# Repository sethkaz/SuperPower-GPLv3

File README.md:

# Super Power RPi Project

This repo was created to make a copy of the SuperPower-RPi project under the license GPLv3.

Please refer to the main Repo (https://github.com/SensorsIot/SuperPower) for the latest version.

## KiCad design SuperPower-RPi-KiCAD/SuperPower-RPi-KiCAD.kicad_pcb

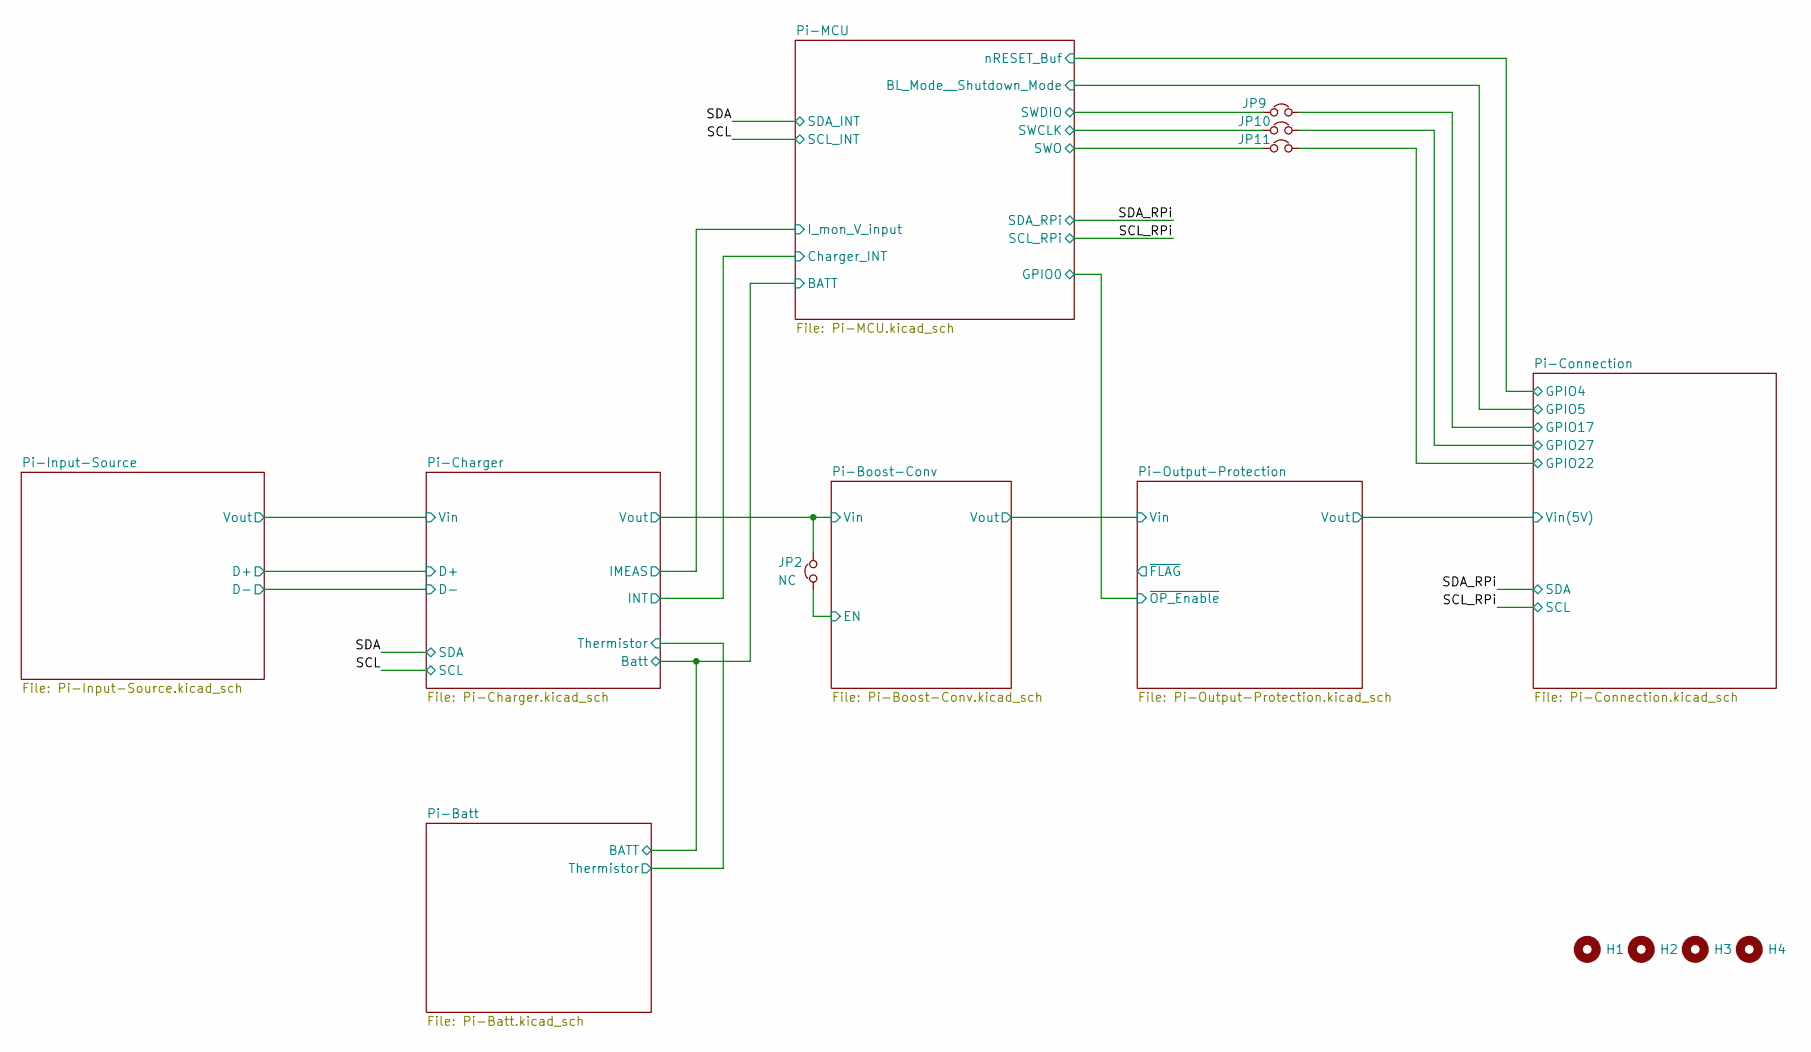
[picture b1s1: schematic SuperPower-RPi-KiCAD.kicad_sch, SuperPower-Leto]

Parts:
H1, H2, H3, H4: DNP; MountingHole_2.7mm_M2.5_ISO14580_Pad_TopBottom
JP2: NC; SolderJumper-2_P1.3mm_Bridged_Pad1.0x1.5mm
JP9, JP10, JP11: Jumper_NC_Small; SolderJumper-2_P1.3mm_Bridged_Pad1.0x1.5mm

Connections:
/Pi-Boost-Conv/EN: JP2.1; also elsewhere on the board
/Pi-Boost-Conv/Vin: JP2.2; also elsewhere on the board
/Pi-Connection/GPIO17: JP9.2; also elsewhere on the board
/Pi-Connection/GPIO22: JP11.2; also elsewhere on the board
/Pi-Connection/GPIO27: JP10.2; also elsewhere on the board
/Pi-MCU/SWCLK: JP10.1; also elsewhere on the board
/Pi-MCU/SWDIO: JP9.1; also elsewhere on the board
/Pi-MCU/SWO: JP11.1; also elsewhere on the board

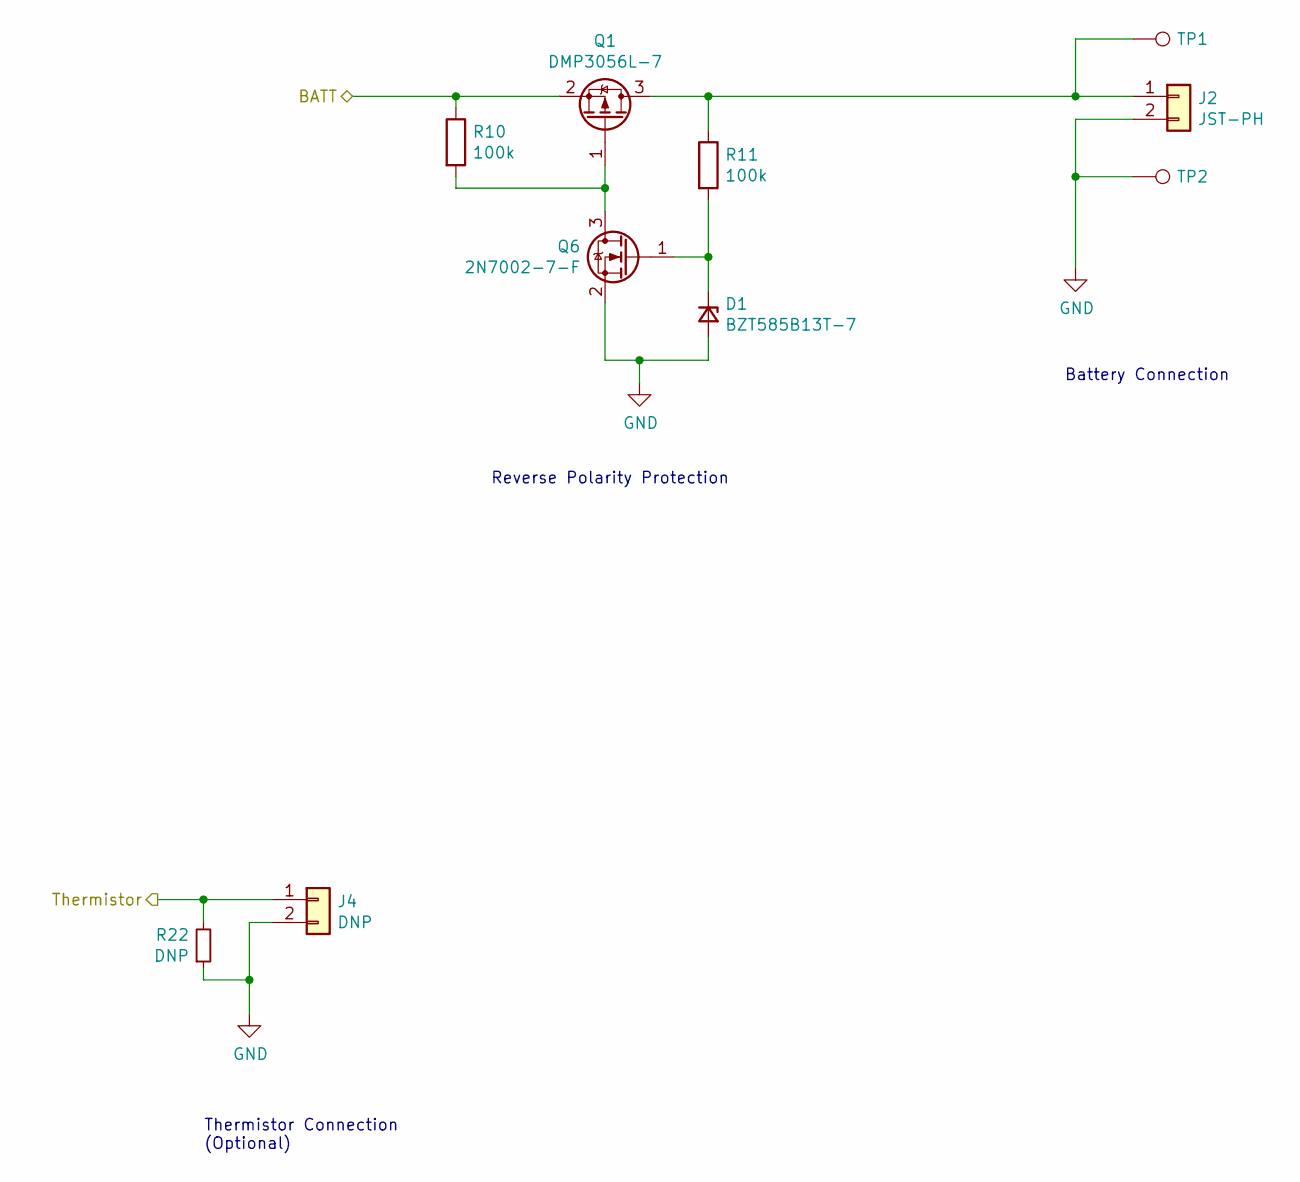
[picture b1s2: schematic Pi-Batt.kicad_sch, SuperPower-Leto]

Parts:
D1: BZT585B13T-7; D_SOD-523; Mfg PN BZT585B13T-7; Digi-Key PN BZT585B13T-7DICT-ND
J2: JST-PH; JST_PH_S2B-PH-K_1x02_P2.00mm_Horizontal; Mfg PN S2B-PH-K-S(LF)(SN)
J4: DNP; PinHeader_1x02_P2.00mm_Vertical; Mfg PN DNP
Q1: Q_PMOS_DMP3056L-7_SOT-23; SOT-23; Mfg PN DMP3056L-7; Digi-Key PN DMP3056L-7DICT-ND
Q6: 2N7002-7-F; SOT-23; Mfg PN 2N7002-7-F; Digi-Key PN 2N7002-FDICT-ND
R10, R11: 100k; R_0402_1005Metric; Mfg PN RC0402FR-07100KL; Digi-Key PN 311-100KLRCT-ND
R22: DNP; R_0603_1608Metric
TP1, TP2: DNP; SolderWire-1.5sqmm_1x01_D1.7mm_OD3.9mm

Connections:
/Pi-Batt/BATT: Q1.2 (S), R10.1; also elsewhere on the board
/Pi-Batt/Thermistor: J4.1, R22.2; also elsewhere on the board
GND: D1.2 (A), J2.2, J4.2, Q6.2 (S), R22.1, TP2.1; also elsewhere on the board
unnamed: D1.1 (K), Q6.1 (G), R11.2
unnamed: J2.1, Q1.3 (D), R11.1, TP1.1
unnamed: Q1.1 (G), Q6.3 (D), R10.2

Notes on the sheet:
Thermistor Connection (Optional)
Reverse Polarity Protection
Battery Connection

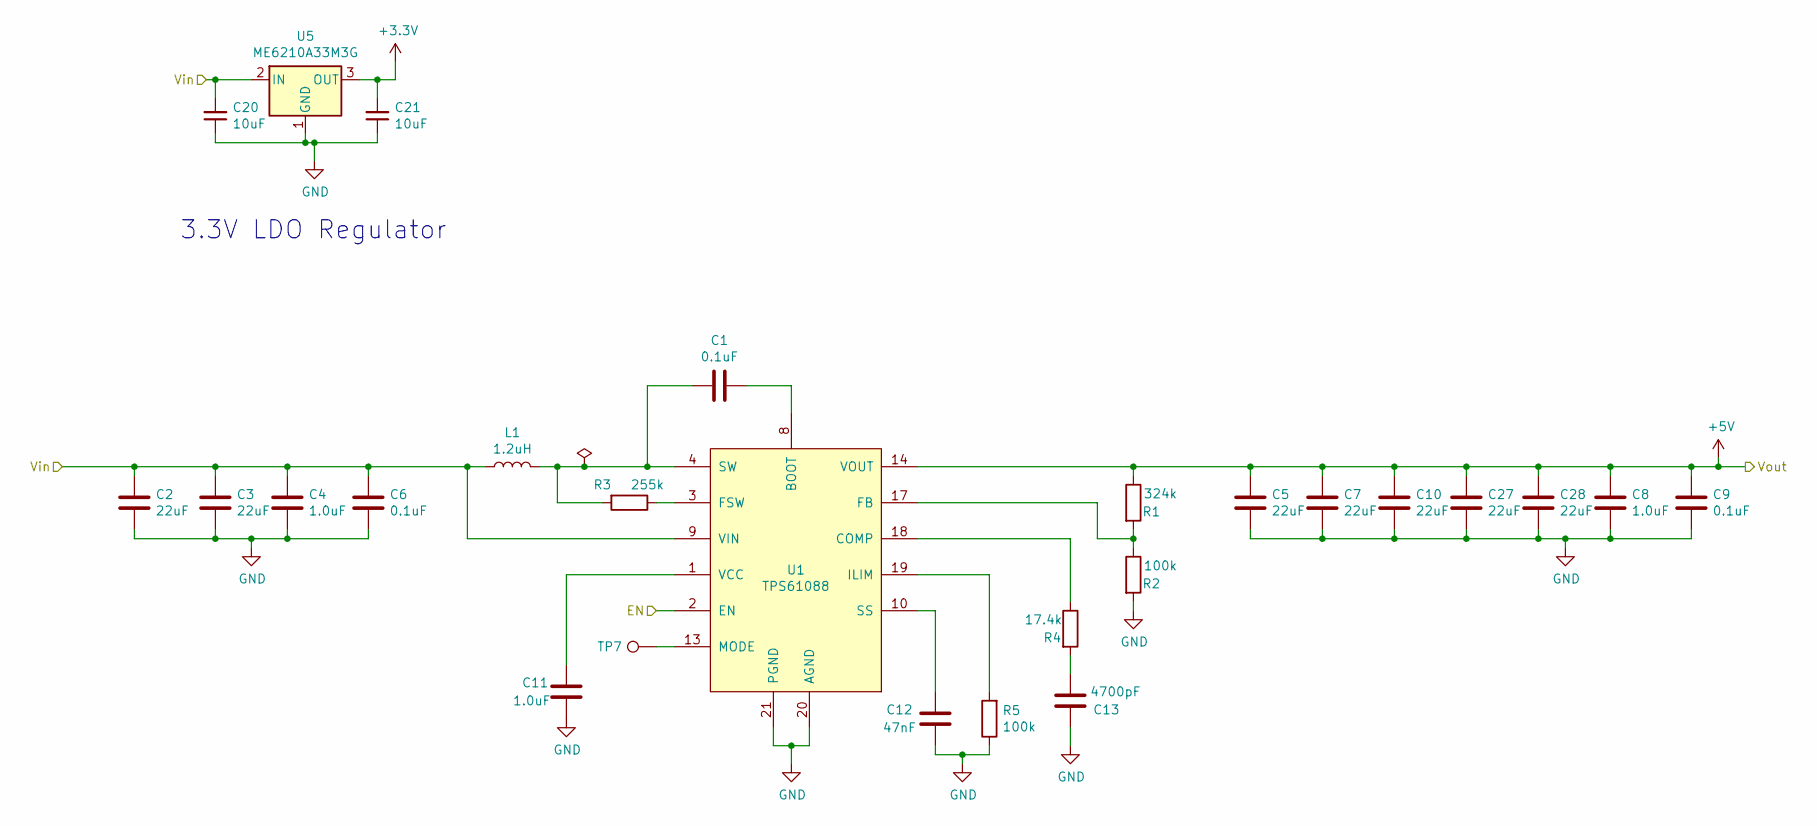
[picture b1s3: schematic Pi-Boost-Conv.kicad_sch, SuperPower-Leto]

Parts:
C1, C6, C9: 0.1uF; C_0402_1005Metric; Mfg PN TMK105BJ104KV-F; Digi-Key PN 587-1456-1-ND
C2, C3, C5, C7, C10, C27, C28: 22uF; C_1206_3216Metric; Mfg PN CL31A226KAHNNNE; Digi-Key PN 1276-3047-1-ND
C4, C8, C11: 1.0uF; C_0402_1005Metric; Mfg PN GRM155R61E105KA12D; Digi-Key PN 490-10017-1-ND
C12: 47nF; C_0402_1005Metric; Mfg PN GRM155R71E473KA88D; Digi-Key PN 490-3254-1-ND
C13: 4700pF; C_0402_1005Metric; Mfg PN CC0402KRX7R8BB472; Digi-Key PN 311-1039-1-ND
C20, C21: 10uF; C_0805_2012Metric; Mfg PN GRM21BR61E106KA73L; Digi-Key PN 490-5523-1-ND
L1: 1.2uH; L_Sumida_CDMC8D28_9.5x8.7mm; Mfg PN CDMC8D28NP-1R2MC; Digi-Key PN 308-1618-1-ND
R1: 324k; R_0402_1005Metric; Mfg PN ERJ-2RKF3243X; Digi-Key PN P324KLCT-ND
R2: 100k; R_0402_1005Metric; Mfg PN RC0402FR-07100KL; Digi-Key PN 311-100KLRCT-ND
R3: 255k; R_0603_1608Metric; Mfg PN RC0603FR-07255KL; Digi-Key PN 311-255KHRCT-ND
R4: 17.4k; R_0402_1005Metric; Mfg PN RC0402FR-0717K4L; Digi-Key PN 311-17.4KLRCT-ND
R5: 100k; R_0603_1608Metric; Mfg PN RC0603FR-07100KL; Digi-Key PN 311-100KHRCT-ND
TP7: DNP; TestPoint_Pad_1.0x1.0mm
U1: TPS61088; TI_VQFN_3.5x4.5mm; Mfg PN TPS61088RHLR; Digi-Key PN 296-43620-1-ND
U5: ME6210A33M3G; SOT-23; Mfg PN ME6210A33M3G

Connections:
+3V3: C21.2, U5.3 (OUT); also elsewhere on the board
+5V: C5.1, C7.1, C8.1, C9.1, C10.1, C27.1, C28.1, R1.1, U1.14 (VOUT), U1.15 (VOUT), U1.16 (VOUT); also elsewhere on the board
/Pi-Boost-Conv/EN: U1.2 (EN); also elsewhere on the board
/Pi-Boost-Conv/Vin: C2.1, C3.1, C4.1, C6.1, C20.2, L1.1, U1.9 (VIN), U5.2 (IN); also elsewhere on the board
GND: C2.2, C3.2, C4.2, C5.2, C6.2, C7.2, C8.2, C9.2, C10.2, C11.2, C12.1, C13.2, C20.1, C21.1, C27.2, C28.2, R2.2, R5.1, U1.11 (NC), U1.12 (NC), U1.20 (AGND), U1.21 (PGND), U5.1 (GND); also elsewhere on the board
unnamed: C1.1, U1.8 (BOOT)
unnamed: C1.2, L1.2, R3.2, U1.4 (SW), U1.5 (SW), U1.6 (SW), U1.7 (SW)
unnamed: C11.1, U1.1 (VCC)
unnamed: C12.2, U1.10 (SS)
unnamed: C13.1, R4.2
unnamed: R1.2, R2.1, U1.17 (FB)
unnamed: R3.1, U1.3 (FSW)
unnamed: R4.1, U1.18 (COMP)
unnamed: R5.2, U1.19 (ILIM)
unnamed: TP7.1, U1.13 (MODE)

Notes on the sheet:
3.3V LDO Regulator

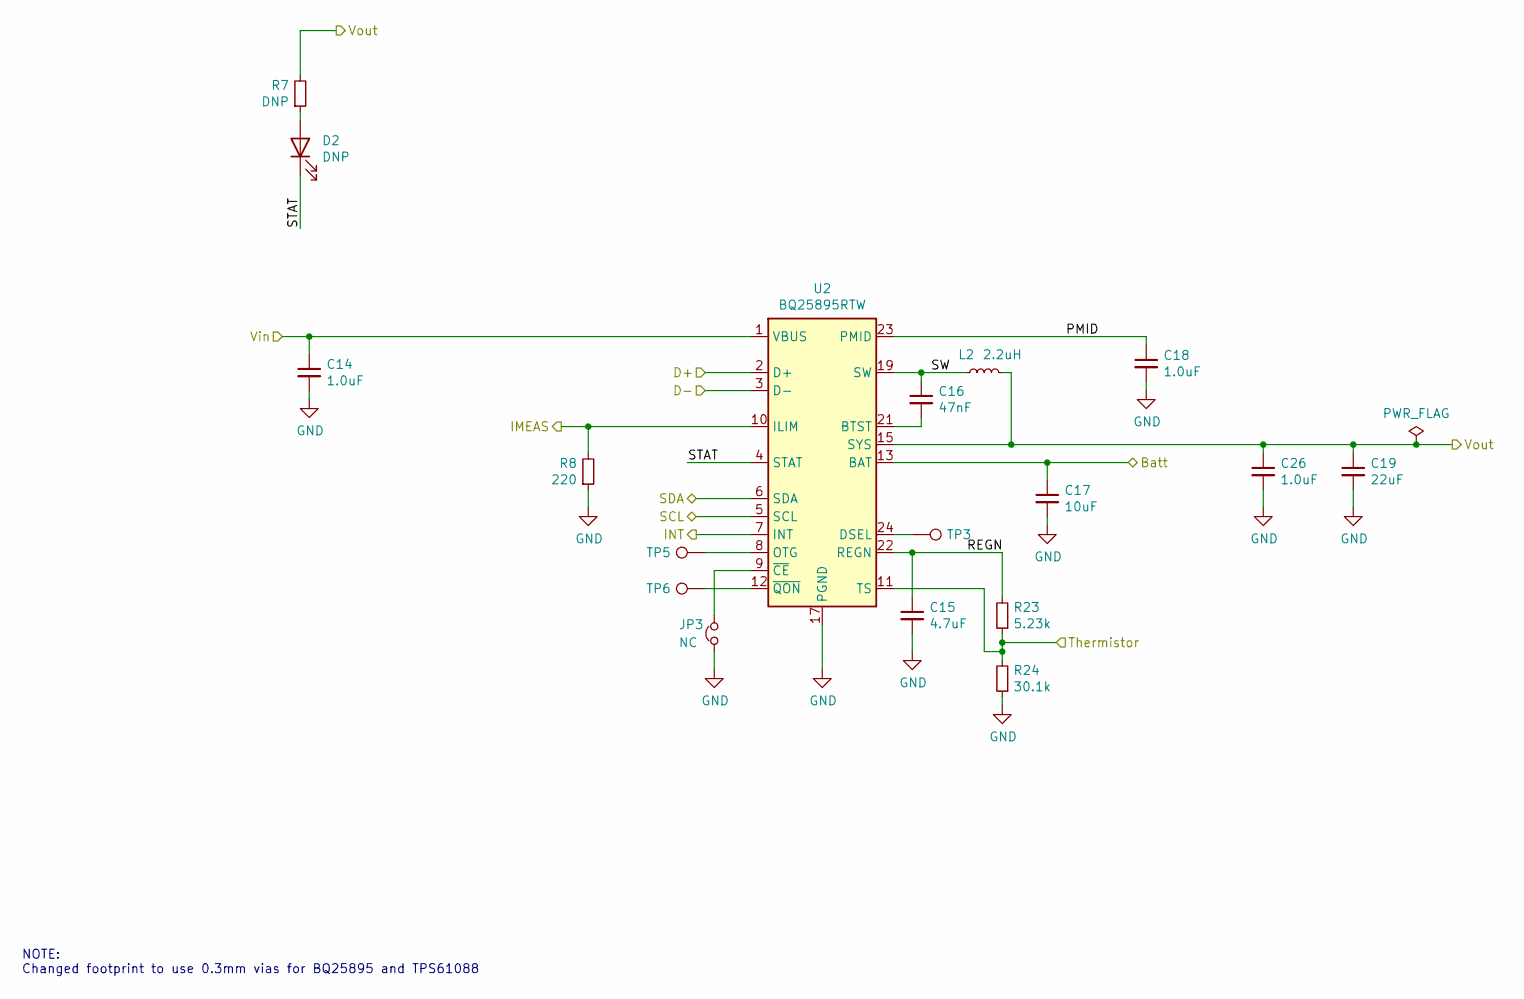
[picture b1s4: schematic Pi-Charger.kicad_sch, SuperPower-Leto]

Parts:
C14, C18, C26: 1.0uF; C_0402_1005Metric; Mfg PN GRM155R61E105KA12D; Digi-Key PN 490-10017-1-ND
C15: 4.7uF; C_0603_1608Metric; Mfg PN CL10A475KA8NQNC; Digi-Key PN 1276-1900-1-ND
C16: 47nF; C_0402_1005Metric; Mfg PN GRM155R71E473KA88D; Digi-Key PN 490-3254-1-ND
C17: 10uF; C_0805_2012Metric; Mfg PN GRM21BR61E106KA73L; Digi-Key PN 490-5523-1-ND
C19: 22uF; C_1206_3216Metric; Mfg PN CL31A226KAHNNNE; Digi-Key PN 1276-3047-1-ND
D2: DNP; LED_0603_1608Metric
JP3: NC; SolderJumper-2_P1.3mm_Bridged_Pad1.0x1.5mm
L2: 2.2uH; L_Vishay_IHLP-2525; Mfg PN IHLP2525CZER2R2M01; Digi-Key PN 541-1008-1-ND
R7: DNP; R_0603_1608Metric
R8: 220; R_0603_1608Metric; Mfg PN RC0603FR-07220RL; Digi-Key PN 311-220HRCT-ND
R23: 5.23k; R_0603_1608Metric; Mfg PN RC0603FR-075K23L; Digi-Key PN 311-5.23KHRCT-ND
R24: 30.1k; R_0603_1608Metric; Mfg PN RC0603FR-0730K1L; Digi-Key PN 311-30.1KHRCT-ND
TP3, TP5, TP6: DNP; TestPoint_Pad_1.0x1.0mm
U2: BQ25895RTW; Texas_S-PWQFN-N24_EP2.7x2.7mm_ThermalVias; Mfg PN BQ25895RTWR; Digi-Key PN 296-44345-1-ND

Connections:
/Pi-Batt/BATT: C17.1, U2.13 (BAT), U2.14 (BAT); also elsewhere on the board
/Pi-Batt/Thermistor: R23.1, R24.2, U2.11 (TS); also elsewhere on the board
/Pi-Boost-Conv/Vin: C19.1, C26.1, L2.2, R7.2, U2.15 (SYS), U2.16 (SYS); also elsewhere on the board
/Pi-Charger/D+: U2.2 (D+); also elsewhere on the board
/Pi-Charger/D-: U2.3 (D-); also elsewhere on the board
/Pi-Charger/IMEAS: R8.2, U2.10 (ILIM); also elsewhere on the board
/Pi-Charger/PMID: C18.1, U2.23 (PMID)
/Pi-Charger/REGN: C15.1, R23.2, U2.22 (REGN)
/Pi-Charger/STAT: D2.1 (K), U2.4 (STAT)
/Pi-Charger/SW: C16.1, L2.1, U2.19 (SW), U2.20 (SW)
/Pi-Charger/Vin: C14.1, U2.1 (VBUS); also elsewhere on the board
/Pi-MCU/Charger_INT: U2.7 (INT); also elsewhere on the board
/SCL: U2.5 (SCL); also elsewhere on the board
/SDA: U2.6 (SDA); also elsewhere on the board
GND: C14.2, C15.2, C17.2, C18.2, C19.2, C26.2, JP3.1, R8.1, R24.1, U2.17 (PGND), U2.18 (PGND), U2.25 (PGND); also elsewhere on the board
unnamed: C16.2, U2.21 (BTST)
unnamed: D2.2 (A), R7.1
unnamed: JP3.2, U2.9 (~CE)
unnamed: TP3.1, U2.24 (DSEL)
unnamed: TP5.1, U2.8 (OTG)
unnamed: TP6.1, U2.12 (~QON)

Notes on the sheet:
NOTE: Changed footprint to use 0.3mm vias for BQ25895 and TPS61088

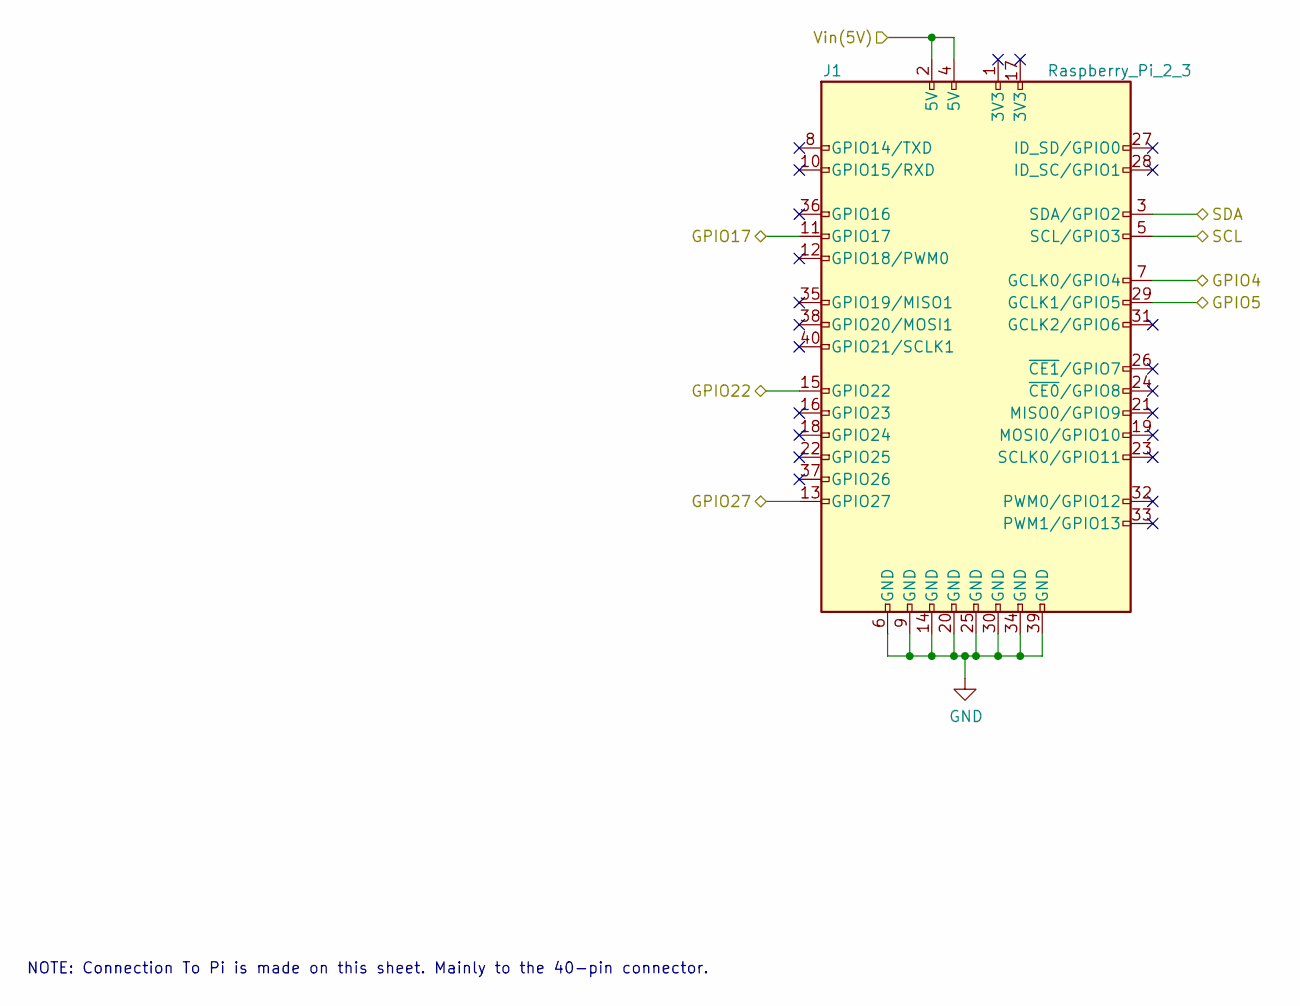
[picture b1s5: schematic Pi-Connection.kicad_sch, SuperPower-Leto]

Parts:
J1: Raspberry_Pi_2_3; PinSocket_2x20_P2.54mm_Vertical_With_Pogo

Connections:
/Pi-Connection/GPIO4: J1.7 (GCLK0/GPIO4); also elsewhere on the board
/Pi-Connection/GPIO17: J1.11 (GPIO17); also elsewhere on the board
/Pi-Connection/GPIO22: J1.15 (GPIO22); also elsewhere on the board
/Pi-Connection/GPIO27: J1.13 (GPIO27); also elsewhere on the board
/Pi-Connection/Vin(5V): J1.2 (5V), J1.4 (5V); also elsewhere on the board
/Pi-MCU/BL_Mode__Shutdown_Mode: J1.29 (GCLK1/GPIO5); also elsewhere on the board
/SCL_RPi: J1.5 (SCL/GPIO3); also elsewhere on the board
/SDA_RPi: J1.3 (SDA/GPIO2); also elsewhere on the board
GND: J1.6 (GND), J1.9 (GND), J1.14 (GND), J1.20 (GND), J1.25 (GND), J1.30 (GND), J1.34 (GND), J1.39 (GND); also elsewhere on the board

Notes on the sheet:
NOTE: Connection To Pi is made on this sheet. Mainly to the 40-pin connector.

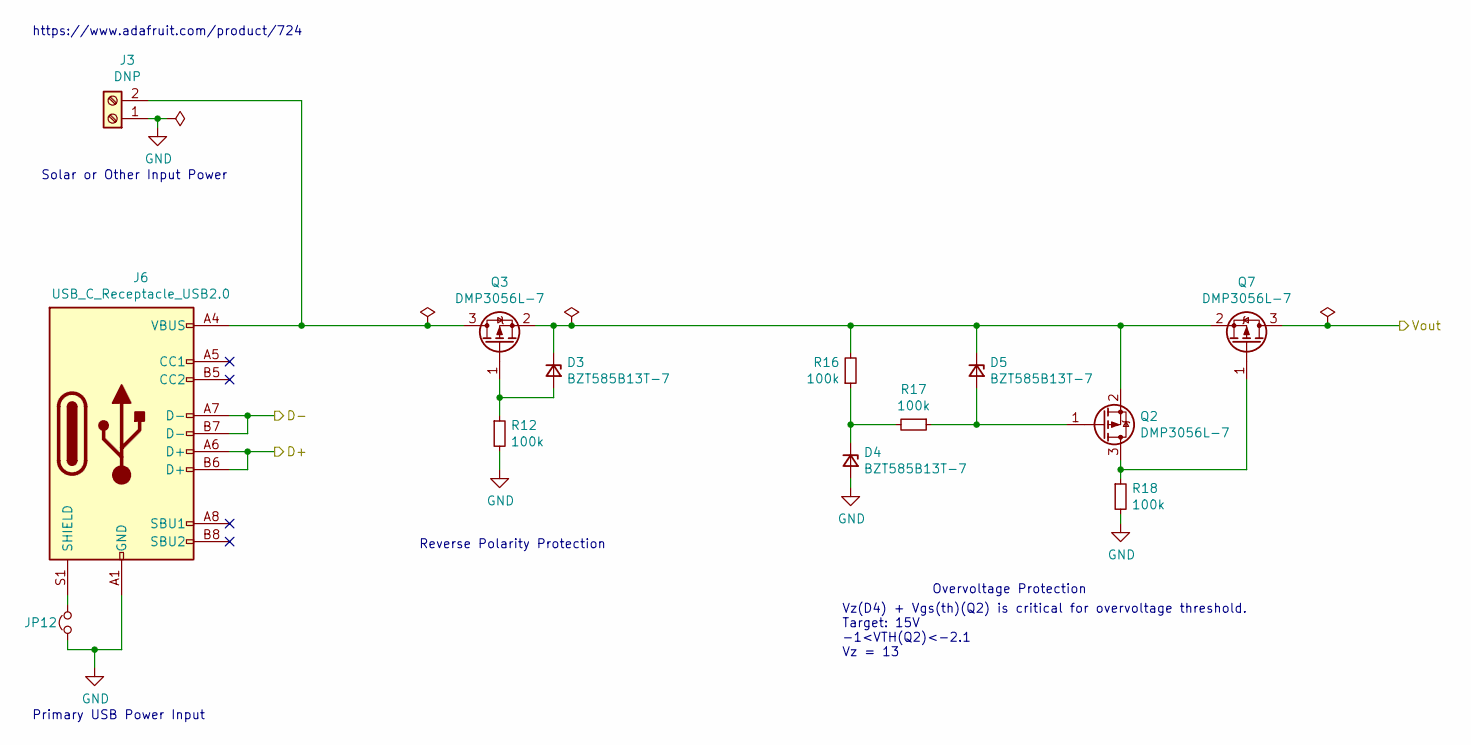
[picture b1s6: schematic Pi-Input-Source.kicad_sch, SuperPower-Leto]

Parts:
D3, D4, D5: BZT585B13T-7; D_SOD-523; Mfg PN BZT585B13T-7; Digi-Key PN BZT585B13T-7DICT-ND
J3: DNP; TerminalBlock_4Ucon_1x02_P3.50mm_Horizontal; Mfg PN 724
J6: USB_C_Receptacle_USB2.0; USB_C_Receptacle_HRO_TYPE-C-31-M-12; Mfg PN TYPE-C-31-M-12
JP12: Jumper_NC_Small; SolderJumper-2_P1.3mm_Bridged_Pad1.0x1.5mm
Q2, Q3, Q7: Q_PMOS_DMP3056L-7_SOT-23; SOT-23; Mfg PN DMP3056L-7; Digi-Key PN DMP3056L-7DICT-ND
R12, R16, R17, R18: 100k; R_0402_1005Metric; Mfg PN RC0402FR-07100KL; Digi-Key PN 311-100KLRCT-ND

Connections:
/Pi-Charger/D+: J6.A6 (D+), J6.B6 (D+); also elsewhere on the board
/Pi-Charger/D-: J6.A7 (D-), J6.B7 (D-); also elsewhere on the board
/Pi-Charger/Vin: Q7.3 (D); also elsewhere on the board
GND: D4.2 (A), J3.1, J6.A1 (GND), J6.A12 (GND), J6.B1 (GND), J6.B12 (GND), JP12.1, R12.2, R18.2; also elsewhere on the board
unnamed: D3.1 (K), D5.1 (K), Q2.2 (S), Q3.2 (S), Q7.2 (S), R16.2
unnamed: D3.2 (A), Q3.1 (G), R12.1
unnamed: D4.1 (K), R16.1, R17.2
unnamed: D5.2 (A), Q2.1 (G), R17.1
unnamed: J3.2, J6.A4 (VBUS), J6.A9 (VBUS), J6.B4 (VBUS), J6.B9 (VBUS), Q3.3 (D)
unnamed: J6.S1 (SHIELD), JP12.2
unnamed: Q2.3 (D), Q7.1 (G), R18.1

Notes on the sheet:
https://www.adafruit.com/product/724
Primary USB Power Input
Solar or Other Input Power
Reverse Polarity Protection
Vz(D4) + Vgs(th)(Q2) is critical for overvoltage threshold. Target: 15V -1<VTH(Q2)<-2.1 Vz = 13
Overvoltage Protection

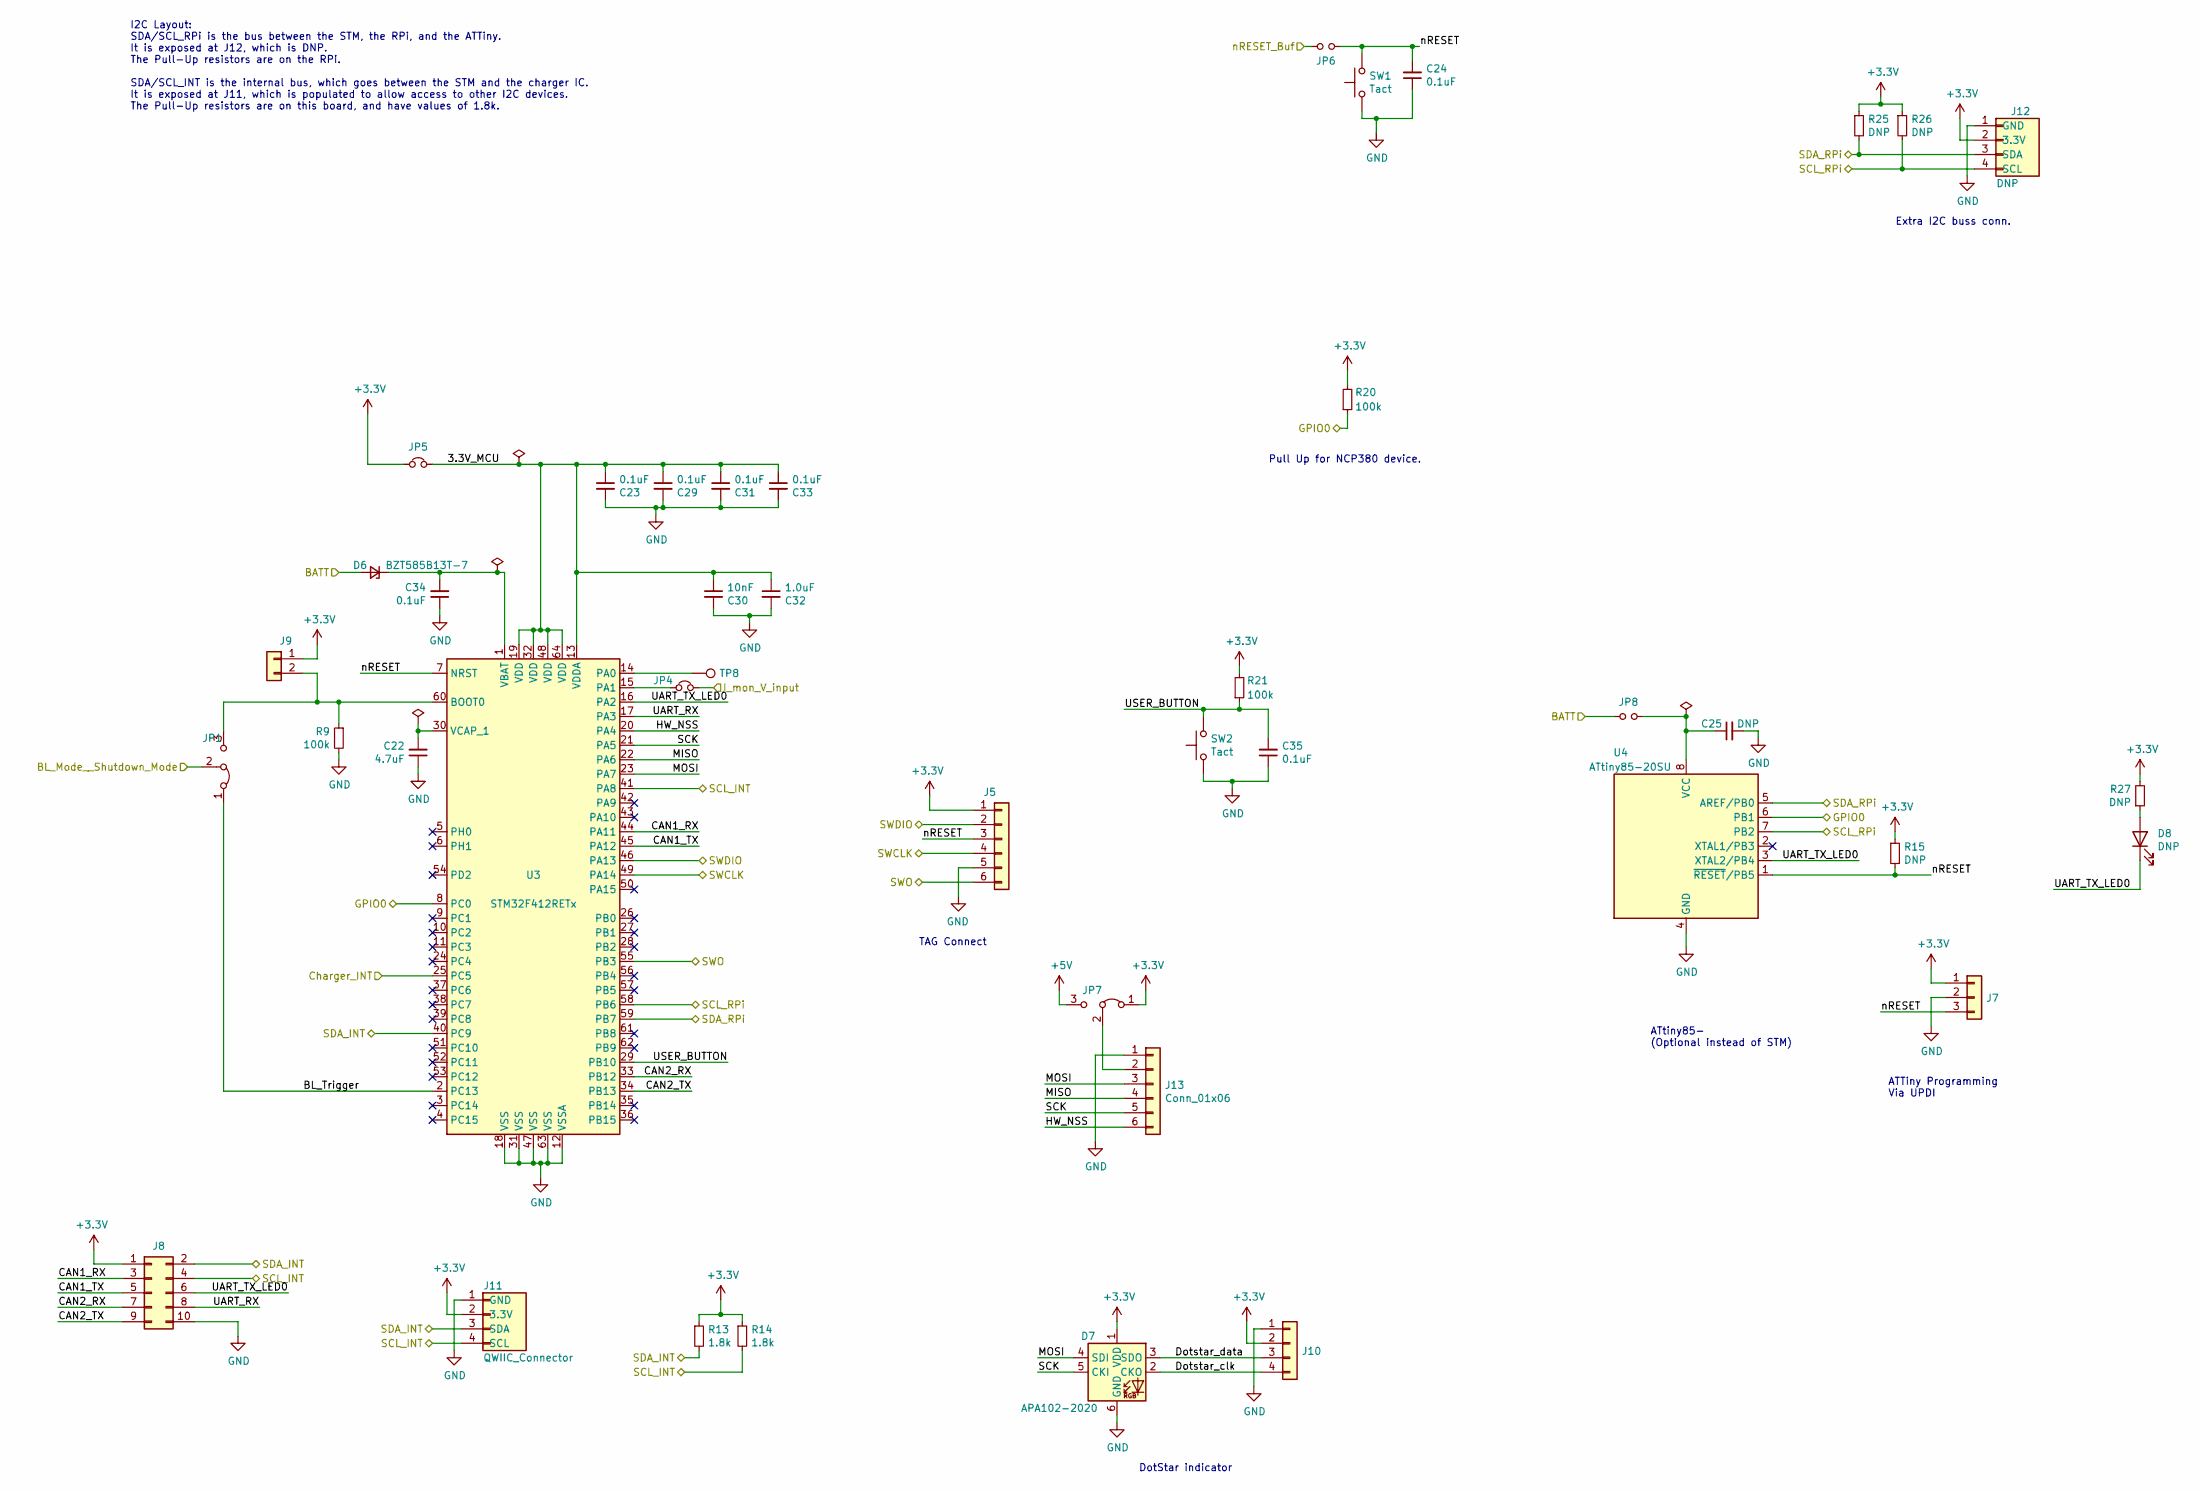
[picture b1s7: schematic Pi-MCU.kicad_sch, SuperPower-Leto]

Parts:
C22: 4.7uF; C_0603_1608Metric; Mfg PN CL10A475KA8NQNC; Digi-Key PN 1276-1900-1-ND
C23, C24, C29, C31, C33, C34, C35: 0.1uF; C_0402_1005Metric; Mfg PN TMK105BJ104KV-F; Digi-Key PN 587-1456-1-ND
C25: DNP; C_0603_1608Metric
C30: 10nF; C_0402_1005Metric; Mfg PN GCM155R71H103KA55D; Digi-Key PN 490-4762-1-ND
C32: 1.0uF; C_0402_1005Metric; Mfg PN GRM155R61E105KA12D; Digi-Key PN 490-10017-1-ND
D6: BZT585B13T-7; D_SOD-523; Mfg PN BZT585B13T-7; Digi-Key PN BZT585B13T-7DICT-ND
D7: APA102-2020; LED-APA102-2020
D8: DNP; LED_0603_1608Metric
J5: DNP; Tag-Connect_TC2030-IDC-NL_2x03_P1.27mm_Vertical; Mfg PN DNP
J7: Conn_01x03; PinHeader_1x03_P2.54mm_Vertical
J8: Conn_02x05_Odd_Even; PinHeader_2x05_P2.54mm_Vertical
J9: Conn_01x02; PinHeader_1x02_P2.54mm_Vertical
J10: Conn_01x04; PinHeader_1x04_P2.54mm_Vertical
J11: QWIIC_Connector; JST_SH_SM04B-SRSS-TB_1x04-1MP_P1.00mm_Horizontal; Mfg PN SM04B-SRSS-TB(LF)(SN); Digi-Key PN 455-1804-1-ND
J12: DNP; JST_SH_SM04B-SRSS-TB_1x04-1MP_P1.00mm_Horizontal; Mfg PN SM04B-SRSS-TB(LF)(SN); Digi-Key PN 455-1804-1-ND
J13: Conn_01x06; PinHeader_1x06_P2.54mm_Vertical
JP1, JP7: DNP; SolderJumper-3_P1.3mm_Bridged12_RoundedPad1.0x1.5mm_NumberL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
JP4: NC; SolderJumper-2_P1.3mm_Bridged_Pad1.0x1.5mm
JP5: Jumper_NC_Small; PinHeader_1x02_P2.54mm_Vertical_Shorted
JP6, JP8: Jumper_NO_Small; SolderJumper-2_P1.3mm_Open_Pad1.0x1.5mm
R9, R20, R21: 100k; R_0402_1005Metric; Mfg PN RC0402FR-07100KL; Digi-Key PN 311-100KLRCT-ND
R13, R14: 1.8k; R_0603_1608Metric; Mfg PN RC0603FR-071K8L; Digi-Key PN 311-1.80KHRCT-ND
R15, R25, R26, R27: DNP; R_0603_1608Metric
SW1, SW2: Tact; SW_Push_1P1T-SH_NO_CK_KMR2xxG; Mfg PN KMR221GLFS; Digi-Key PN 401-1427-1-ND
TP8: DNP; TestPoint_Pad_1.0x1.0mm
U3: STM32F412RETx; LQFP-64_10x10mm_P0.5mm; Mfg PN STM32F412RET6; Digi-Key PN 497-19350-1-ND
U4: ATtiny85-20SU; SOIJ-8_5.3x5.3mm_P1.27mm

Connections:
+3V3: D7.1 (VDD), J5.1, J7.1, J8.1, J9.1, J10.2, J11.2 (3.3V), J12.2 (3.3V), JP5.1, JP7.1 (A), R13.1, R14.1, R15.1, R20.2, R21.2, R25.1, R26.1, R27.2; also elsewhere on the board
+5V: JP7.3 (B); also elsewhere on the board
/Pi-Batt/BATT: D6.2 (A), JP8.2; also elsewhere on the board
/Pi-Charger/IMEAS: JP4.2; also elsewhere on the board
/Pi-Connection/GPIO4: JP6.1; also elsewhere on the board
/Pi-MCU/3.3V_MCU: C23.1, C29.1, C30.1, C31.1, C32.1, C33.1, JP5.2, U3.13 (VDDA), U3.19 (VDD), U3.32 (VDD), U3.48 (VDD), U3.64 (VDD)
/Pi-MCU/BL_Mode__Shutdown_Mode: JP1.2 (C); also elsewhere on the board
/Pi-MCU/BL_Trigger: JP1.1 (A), U3.2 (PC13)
/Pi-MCU/CAN1_RX: J8.3, U3.44 (PA11)
/Pi-MCU/CAN1_TX: J8.5, U3.45 (PA12)
/Pi-MCU/CAN2_RX: J8.7, U3.33 (PB12)
/Pi-MCU/CAN2_TX: J8.9, U3.34 (PB13)
/Pi-MCU/Charger_INT: U3.25 (PC5); also elsewhere on the board
/Pi-MCU/Dotstar_clk: D7.2 (CKO), J10.4
/Pi-MCU/Dotstar_data: D7.3 (SDO), J10.3
/Pi-MCU/GPIO0: R20.1, U3.8 (PC0), U4.6 (PB1); also elsewhere on the board
/Pi-MCU/HW_NSS: J13.6, U3.20 (PA4)
/Pi-MCU/MISO: J13.4, U3.22 (PA6)
/Pi-MCU/MOSI: D7.4 (SDI), J13.3, U3.23 (PA7)
/Pi-MCU/SCK: D7.5 (CKI), J13.5, U3.21 (PA5)
/Pi-MCU/SWCLK: J5.4, U3.49 (PA14); also elsewhere on the board
/Pi-MCU/SWDIO: J5.2, U3.46 (PA13); also elsewhere on the board
/Pi-MCU/SWO: J5.6, U3.55 (PB3); also elsewhere on the board
/Pi-MCU/UART_RX: J8.8, U3.17 (PA3)
/Pi-MCU/UART_TX_LED0: D8.1 (K), J8.6, U3.16 (PA2), U4.3 (XTAL2/PB4)
/Pi-MCU/USER_BUTTON: C35.2, R21.1, SW2.2, U3.29 (PB10)
/Pi-MCU/nRESET: C24.2, J5.3, J7.3, JP6.2, R15.2, SW1.2, U3.7 (NRST), U4.1 (~RESET~/PB5)
/SCL: J8.4, J11.4 (SCL), R14.2, U3.41 (PA8); also elsewhere on the board
/SCL_RPi: J12.4 (SCL), R26.2, U3.58 (PB6), U4.7 (PB2); also elsewhere on the board
/SDA: J8.2, J11.3 (SDA), R13.2, U3.40 (PC9); also elsewhere on the board
/SDA_RPi: J12.3 (SDA), R25.2, U3.59 (PB7), U4.5 (AREF/PB0); also elsewhere on the board
GND: C22.1, C23.2, C24.1, C25.2, C29.2, C30.2, C31.2, C32.2, C33.2, C34.1, C35.1, D7.6 (GND), J5.5, J7.2, J8.10, J10.1, J11.1 (GND), J12.1 (GND), J13.1, R9.2, SW1.1, SW2.1, U3.12 (VSSA), U3.18 (VSS), U3.31 (VSS), U3.47 (VSS), U3.63 (VSS), U4.4 (GND); also elsewhere on the board
unnamed: C22.2, U3.30 (VCAP_1)
unnamed: C25.1, JP8.1, U4.8 (VCC)
unnamed: C34.2, D6.1 (K), U3.1 (VBAT)
unnamed: D8.2 (A), R27.1
unnamed: J9.2, JP1.3 (B), R9.1, U3.60 (BOOT0)
unnamed: J13.2, JP7.2 (C)
unnamed: JP4.1, U3.15 (PA1)
unnamed: TP8.1, U3.14 (PA0)

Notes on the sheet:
I2C Layout: SDA/SCL_RPi is the bus between the STM, the RPi, and the ATTiny. It is exposed at J12, which is DNP. The Pull-Up resistors are on the RPi. SDA/SCL_INT is the internal bus, which goes between the STM and the charger IC. It is exposed at J11, which is populated to allow access to other I2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
TAG Connect
DotStar indicator
Pull Up for NCP380 device.
ATtiny85- (Optional instead of STM)
ATTiny Programming Via UPDI
Extra I2C buss conn.

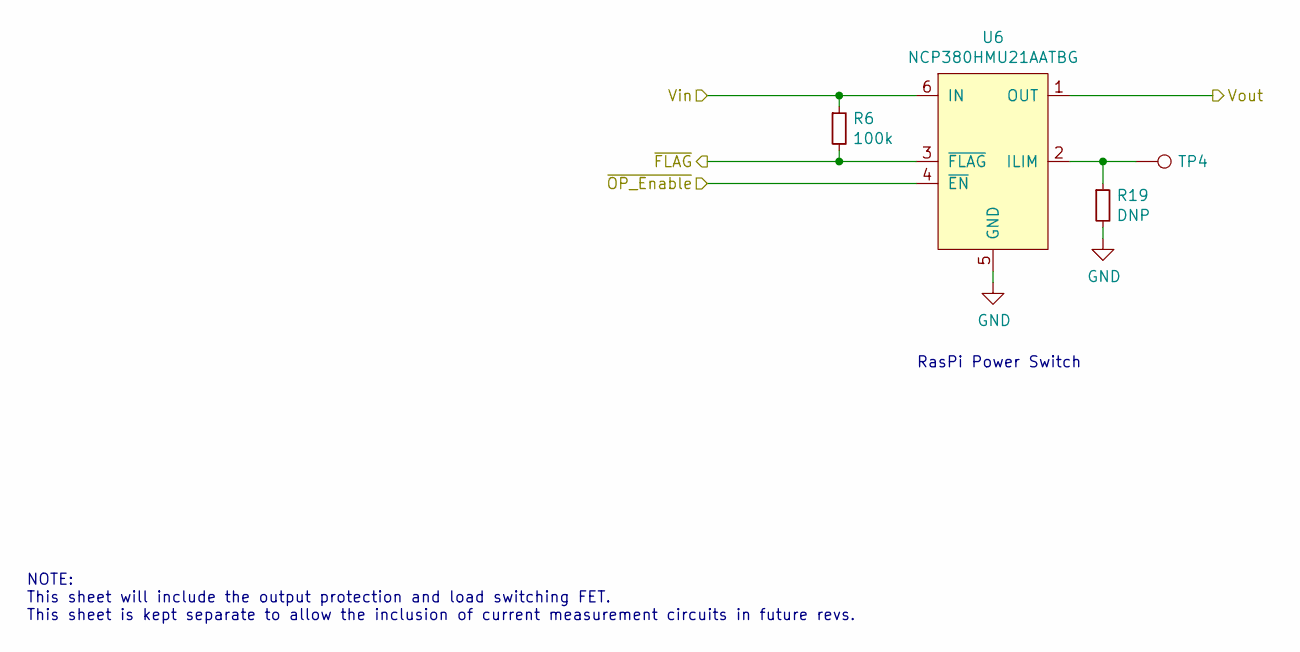
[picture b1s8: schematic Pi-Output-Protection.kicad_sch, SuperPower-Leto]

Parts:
R6: 100k; R_0402_1005Metric; Mfg PN RC0402FR-07100KL; Digi-Key PN 311-100KLRCT-ND
R19: DNP; R_0603_1608Metric; Mfg PN DNP; Digi-Key PN DNP
TP4: DNP; TestPoint_Pad_1.0x1.0mm
U6: NCP380HMU21AATBG; UDFN-6-1EP_2x2mm_P0.65mm_EP0.95x1.7mm; Mfg PN NCP380HMU21AATBG; Digi-Key PN NCP380HMU21AATBGOSCT-ND

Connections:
+5V: R6.1, U6.6 (IN); also elsewhere on the board
/Pi-Connection/Vin(5V): U6.1 (OUT); also elsewhere on the board
/Pi-MCU/GPIO0: U6.4 (~EN); also elsewhere on the board
/Pi-Output-Protection/~FLAG: R6.2, U6.3 (~FLAG)
GND: R19.2, U6.5 (GND), U6.7 (PAD); also elsewhere on the board
unnamed: R19.1, TP4.1, U6.2 (ILIM)

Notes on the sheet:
NOTE: This sheet will include the output protection and load switching FET. This sheet is kept separate to allow the inclusion of current measurement circuits in future revs.
RasPi Power Switch
